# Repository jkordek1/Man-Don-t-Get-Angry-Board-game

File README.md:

# Man, Don't Get Angry - Board game

## About

Mensch ärgere Dich nicht (English: Man, Don't Get Angry) is a German board game developed by Josef Friedrich Schmidt in 1907/1908.
The name derives from the fact that a peg is sent back to the "out" field when another peg lands on it, similar to the later game Sorry!.

More information about the game can be found at the [wiki page](https://en.wikipedia.org/wiki/Mensch_%C3%A4rgere_Dich_nicht).

## Project idea
Idea of the project is to create an electronic version of the game to help promoting STEM education (and to have some fun of course).

## Project status
- [x] Breadboard prototype
- [x] Schematic
- [x] PCBs
- [x] Enclosure design
- [x] 3D CAD assembly and renders
- [x] Assembly
- [ ] Programming

## Issues
- no active issues

## Main features
- Based on popular ATmega328p microcontroller used on Arduino boards
- WS2812B-V5 addressable LEDs with no external components needed
- WS2812-mini addressable LED used as battery level indicator
- Touchpads connected via PCF8575 I/O Expander used as controls
- Piezo buzzer for audio queues
- 3000mAh rechargable Li-Po battery
- USB-C connector for charging and programming the microcontroller

## 3D renders

## Images

## PCBs
There are 3 different PCBs:

**BoardGame** - main 150x150mm PCB that contains LEDs and most of the electronic components (1 needed)

**Dice** - small PCB used as a touchpad (1 needed)

**Touchpad** - PCB with 3 touchpads used as controls for the game (4 needed)

## Enclosure
There are few 3D models files needed for enclosure:
1. Case - main part of the enclosure
2. FieldBoard - Upper part of the enclosure printed with black and white filaments

## Project folder structure
    .
    ├── ...
    ├── Images                  # Images of the project
    ├── Solidworks assembly     # Enclosure and PCB 3D model files
    ├── KiCad files             # Main folder
    │   ├── 3D models           # 3d models of components
    │   ├── BoardGame           # KiCAD project for main PCB
    │   ├── Dice                # KiCAD project for dice
    │   └── Touchpad            # KiCAD project for touchpad controls
    └── ...

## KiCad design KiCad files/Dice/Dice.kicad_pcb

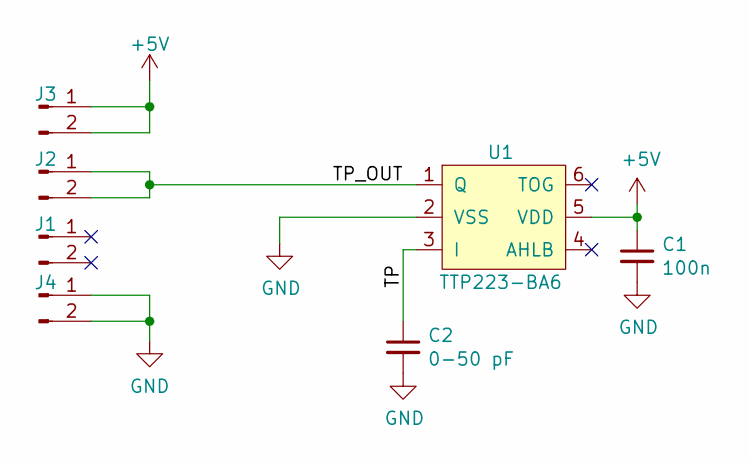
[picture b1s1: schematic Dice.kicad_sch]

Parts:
C1: 100n; C_0603_1608Metric
C2: 0-50 pF; C_0603_1608Metric
J1, J2, J3, J4: Conn_01x02_Male; PinHeader_1x02_P1.27mm_Vertical_SMD_Pin1Left
U1: TTP223-BA6; SOT-23-6

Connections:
+5V: C1.1, J3.1, J3.2, U1.5 (VDD)
/TP: C2.1, U1.3 (I)
/TP_OUT: J2.1, J2.2, U1.1 (Q)
GND: C1.2, C2.2, J4.1, J4.2, U1.2 (VSS)

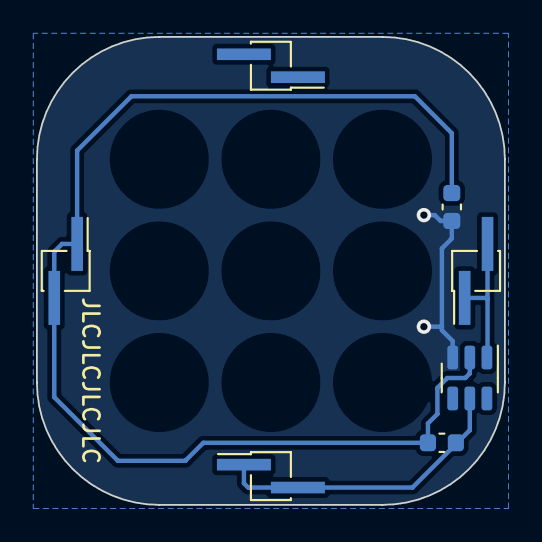
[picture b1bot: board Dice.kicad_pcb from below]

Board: 2 copper layers, 26.0 x 26.0 mm, 7 parts (7 on the bottom side), 4 nets.

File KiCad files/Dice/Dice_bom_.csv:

Component,Description,Part,References,Value,Footprint,Quantity Per PCB,Datasheet
1,"Unpolarized capacitor, small symbol",C_Small,C1,100n,C_0603_1608Metric,1,~
2,"Unpolarized capacitor, small symbol",C_Small,C2,0-50 pF,C_0603_1608Metric,1,~
3,"Generic connector, single row, 01x02, script generated (kicad-library-utils/schlib/autogen/connector/)",Conn_01x02_Male,J1 J2 J3 J4,Conn_01x02_Male,PinHeader_1x02_P1.27mm_Vertical_SMD_Pin1Left,4,~
4,,TTP223-BA6,U1,TTP223-BA6,SOT-23-6,1,





Component Groups:,4
Component Count:,7
Fitted Components:,7
Number of PCBs:,1
Total components:,7
Schematic Version:,
Schematic Date:,
PCB Variant:,default
BoM Date:,10.1.2023. 13:12:25
Schematic Source:,Dice.kicad_sch
KiCad Version:,Eeschema (6.0.10)

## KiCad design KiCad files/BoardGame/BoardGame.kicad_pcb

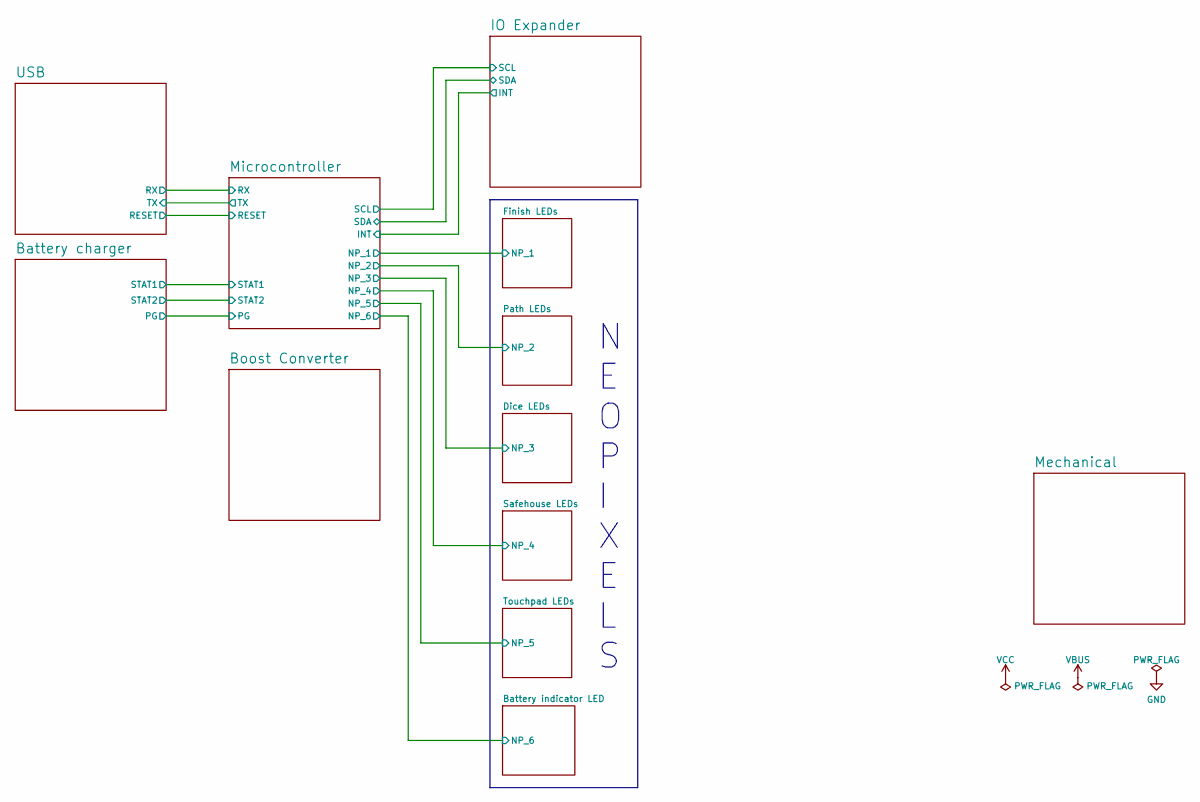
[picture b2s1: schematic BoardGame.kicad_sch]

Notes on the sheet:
N E O P I X E L S

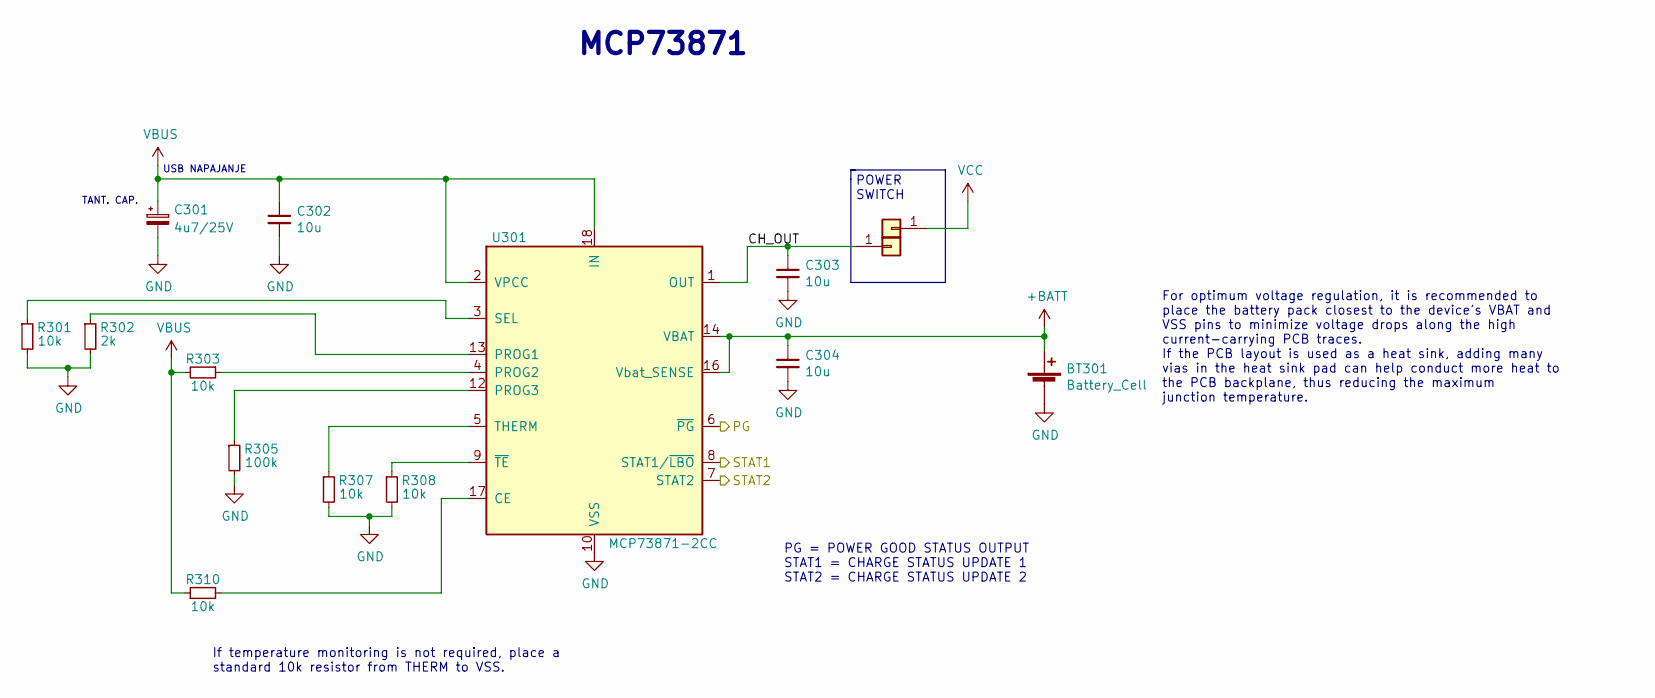
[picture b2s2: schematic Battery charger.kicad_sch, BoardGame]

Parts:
BT301: Battery_Cell; battery_103565_3000mah
C301: 4u7/25V; CP_EIA-3528-21_Kemet-B; JLCPCB Part # C2798040
C302, C303, C304: 10u; C_0805_2012Metric; JLCPCB Part # C237493
J301, J302: Conn_01x01; PinHeader_1x01
R301, R303, R307, R308, R310: 10k; R_0603_1608Metric
R302: 2k; R_0603_1608Metric; JLCPCB Part # C25590
R305: 100k; R_0603_1608Metric
U301: MCP73871-2CC; QFN-20-1EP_4x4mm_P0.5mm_EP2.5x2.5mm

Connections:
+BATT: BT301.1 (+), C304.1, U301.14 (VBAT), U301.15 (VBAT), U301.16 (Vbat_SENSE)
/Battery charger/CH_OUT: C303.1, J302.1, U301.1 (OUT), U301.20 (OUT)
/Battery charger/PG: U301.6 (~PG); also elsewhere on the board
/Battery charger/STAT1: U301.8 (STAT1/~LBO); also elsewhere on the board
/Battery charger/STAT2: U301.7 (STAT2); also elsewhere on the board
GND: BT301.2 (-), C301.2, C302.2, C303.2, C304.2, R301.2, R302.2, R305.2, R307.2, R308.2, U301.10 (VSS), U301.11 (VSS), U301.21 (VSS); also elsewhere on the board
unnamed: R310.2, U301.17 (CE)
unnamed: R302.1, U301.13 (PROG1)
unnamed: R303.1, U301.4 (PROG2)
unnamed: R305.1, U301.12 (PROG3)
unnamed: R301.1, U301.3 (SEL)
unnamed: R307.1, U301.5 (THERM)
unnamed: R308.1, U301.9 (~TE)
VBUS: C301.1, C302.1, R303.2, R310.1, U301.2 (VPCC), U301.18 (IN), U301.19 (IN); also elsewhere on the board
VCC: J301.1; also elsewhere on the board

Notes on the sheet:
PG = POWER GOOD STATUS OUTPUT STAT1 = CHARGE STATUS UPDATE 1 STAT2 = CHARGE STATUS UPDATE 2
TANT. CAP.
USB NAPAJANJE
POWER SWITCH
For optimum voltage regulation, it is recommended to place the battery pack closest to the device's VBAT and VSS pins to minimize voltage drops along the high current-carrying PCB traces. If the PCB layout is used as a heat sink, adding many vias in the heat sink pad can help conduct more heat to t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
MCP73871
If temperature monitoring is not required, place a standard 10k resistor from THERM to VSS.

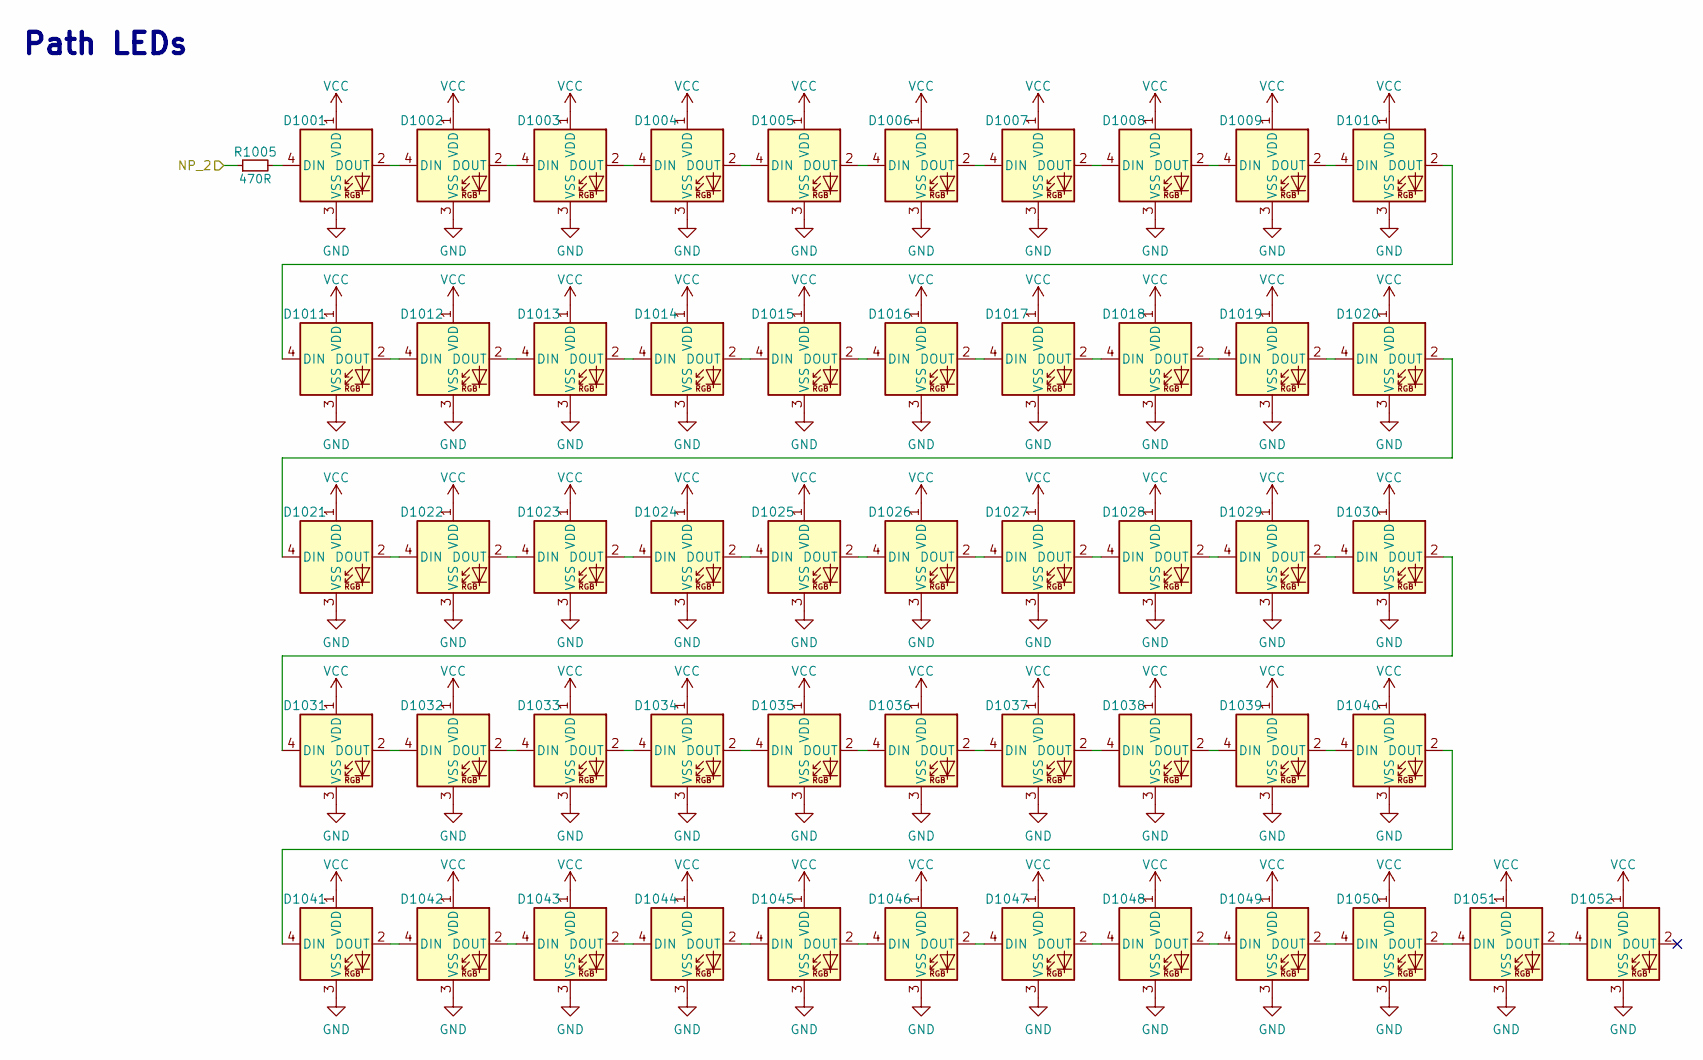
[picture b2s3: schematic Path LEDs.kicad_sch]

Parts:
D1001, D1002, D1003, D1004, D1005, D1006, D1007, D1008, D1009, D1010, D1011, D1012, D1013, D1014, D1015, D1016, D1017, D1018, D1019, D1020, D1021, D1022, D1023, D1024, D1025, D1026, D1027, D1028, D1029, D1030, D1031, D1032, D1033, D1034, D1035, D1036, D1037, D1038, D1039, D1040, D1041, D1042, D1043, D1044, D1045, D1046, D1047, D1048, D1049, D1050, D1051, D1052: WS2812B; LED_WS2812B_edited
R1005: 470R; R_0603_1608Metric

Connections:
/Microcontroller/NP_2: R1005.1; also elsewhere on the board
GND: D1001.3 (VSS), D1002.3 (VSS), D1003.3 (VSS), D1004.3 (VSS), D1005.3 (VSS), D1006.3 (VSS), D1007.3 (VSS), D1008.3 (VSS), D1009.3 (VSS), D1010.3 (VSS), D1011.3 (VSS), D1012.3 (VSS), D1013.3 (VSS), D1014.3 (VSS), D1015.3 (VSS), D1016.3 (VSS), D1017.3 (VSS), D1018.3 (VSS), D1019.3 (VSS), D1020.3 (VSS), D1021.3 (VSS), D1022.3 (VSS), D1023.3 (VSS), D1024.3 (VSS), D1025.3 (VSS), D1026.3 (VSS), D1027.3 (VSS), D1028.3 (VSS), D1029.3 (VSS), D1030.3 (VSS), D1031.3 (VSS), D1032.3 (VSS), D1033.3 (VSS), D1034.3 (VSS), D1035.3 (VSS), D1036.3 (VSS), D1037.3 (VSS), D1038.3 (VSS), D1039.3 (VSS), D1040.3 (VSS), D1041.3 (VSS), D1042.3 (VSS), D1043.3 (VSS), D1044.3 (VSS), D1045.3 (VSS), D1046.3 (VSS), D1047.3 (VSS), D1048.3 (VSS), D1049.3 (VSS), D1050.3 (VSS), D1051.3 (VSS), D1052.3 (VSS); also elsewhere on the board
unnamed: D1001.4 (DIN), R1005.2
unnamed: D1001.2 (DOUT), D1002.4 (DIN)
unnamed: D1002.2 (DOUT), D1003.4 (DIN)
unnamed: D1003.2 (DOUT), D1004.4 (DIN)
unnamed: D1004.2 (DOUT), D1005.4 (DIN)
unnamed: D1005.2 (DOUT), D1006.4 (DIN)
unnamed: D1006.2 (DOUT), D1007.4 (DIN)
unnamed: D1007.2 (DOUT), D1008.4 (DIN)
unnamed: D1008.2 (DOUT), D1009.4 (DIN)
unnamed: D1009.2 (DOUT), D1010.4 (DIN)
unnamed: D1010.2 (DOUT), D1011.4 (DIN)
unnamed: D1011.2 (DOUT), D1012.4 (DIN)
unnamed: D1012.2 (DOUT), D1013.4 (DIN)
unnamed: D1013.2 (DOUT), D1014.4 (DIN)
unnamed: D1014.2 (DOUT), D1015.4 (DIN)
unnamed: D1015.2 (DOUT), D1016.4 (DIN)
unnamed: D1016.2 (DOUT), D1017.4 (DIN)
unnamed: D1017.2 (DOUT), D1018.4 (DIN)
unnamed: D1018.2 (DOUT), D1019.4 (DIN)
unnamed: D1019.2 (DOUT), D1020.4 (DIN)
unnamed: D1020.2 (DOUT), D1021.4 (DIN)
unnamed: D1021.2 (DOUT), D1022.4 (DIN)
unnamed: D1022.2 (DOUT), D1023.4 (DIN)
unnamed: D1023.2 (DOUT), D1024.4 (DIN)
unnamed: D1024.2 (DOUT), D1025.4 (DIN)
unnamed: D1025.2 (DOUT), D1026.4 (DIN)
unnamed: D1026.2 (DOUT), D1027.4 (DIN)
unnamed: D1027.2 (DOUT), D1028.4 (DIN)
unnamed: D1028.2 (DOUT), D1029.4 (DIN)
unnamed: D1029.2 (DOUT), D1030.4 (DIN)
unnamed: D1030.2 (DOUT), D1031.4 (DIN)
unnamed: D1031.2 (DOUT), D1032.4 (DIN)
unnamed: D1032.2 (DOUT), D1033.4 (DIN)
unnamed: D1033.2 (DOUT), D1034.4 (DIN)
unnamed: D1034.2 (DOUT), D1035.4 (DIN)
unnamed: D1035.2 (DOUT), D1036.4 (DIN)
unnamed: D1036.2 (DOUT), D1037.4 (DIN)
unnamed: D1037.2 (DOUT), D1038.4 (DIN)
unnamed: D1038.2 (DOUT), D1039.4 (DIN)
unnamed: D1039.2 (DOUT), D1040.4 (DIN)
unnamed: D1040.2 (DOUT), D1041.4 (DIN)
unnamed: D1041.2 (DOUT), D1042.4 (DIN)
unnamed: D1042.2 (DOUT), D1043.4 (DIN)
unnamed: D1043.2 (DOUT), D1044.4 (DIN)
unnamed: D1044.2 (DOUT), D1045.4 (DIN)
unnamed: D1045.2 (DOUT), D1046.4 (DIN)
unnamed: D1046.2 (DOUT), D1047.4 (DIN)
unnamed: D1047.2 (DOUT), D1048.4 (DIN)
unnamed: D1048.2 (DOUT), D1049.4 (DIN)
unnamed: D1049.2 (DOUT), D1050.4 (DIN)
unnamed: D1050.2 (DOUT), D1051.4 (DIN)
unnamed: D1051.2 (DOUT), D1052.4 (DIN)
VCC: D1001.1 (VDD), D1002.1 (VDD), D1003.1 (VDD), D1004.1 (VDD), D1005.1 (VDD), D1006.1 (VDD), D1007.1 (VDD), D1008.1 (VDD), D1009.1 (VDD), D1010.1 (VDD), D1011.1 (VDD), D1012.1 (VDD), D1013.1 (VDD), D1014.1 (VDD), D1015.1 (VDD), D1016.1 (VDD), D1017.1 (VDD), D1018.1 (VDD), D1019.1 (VDD), D1020.1 (VDD), D1021.1 (VDD), D1022.1 (VDD), D1023.1 (VDD), D1024.1 (VDD), D1025.1 (VDD), D1026.1 (VDD), D1027.1 (VDD), D1028.1 (VDD), D1029.1 (VDD), D1030.1 (VDD), D1031.1 (VDD), D1032.1 (VDD), D1033.1 (VDD), D1034.1 (VDD), D1035.1 (VDD), D1036.1 (VDD), D1037.1 (VDD), D1038.1 (VDD), D1039.1 (VDD), D1040.1 (VDD), D1041.1 (VDD), D1042.1 (VDD), D1043.1 (VDD), D1044.1 (VDD), D1045.1 (VDD), D1046.1 (VDD), D1047.1 (VDD), D1048.1 (VDD), D1049.1 (VDD), D1050.1 (VDD), D1051.1 (VDD), D1052.1 (VDD); also elsewhere on the board

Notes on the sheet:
Path LEDs

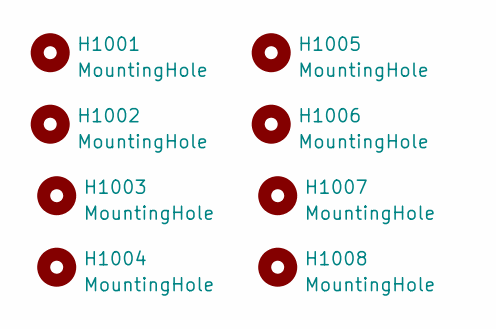
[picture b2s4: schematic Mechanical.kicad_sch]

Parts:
H1001, H1002, H1003, H1004, H1005, H1006, H1007, H1008: MountingHole; MountingHole_3.2mm_M3

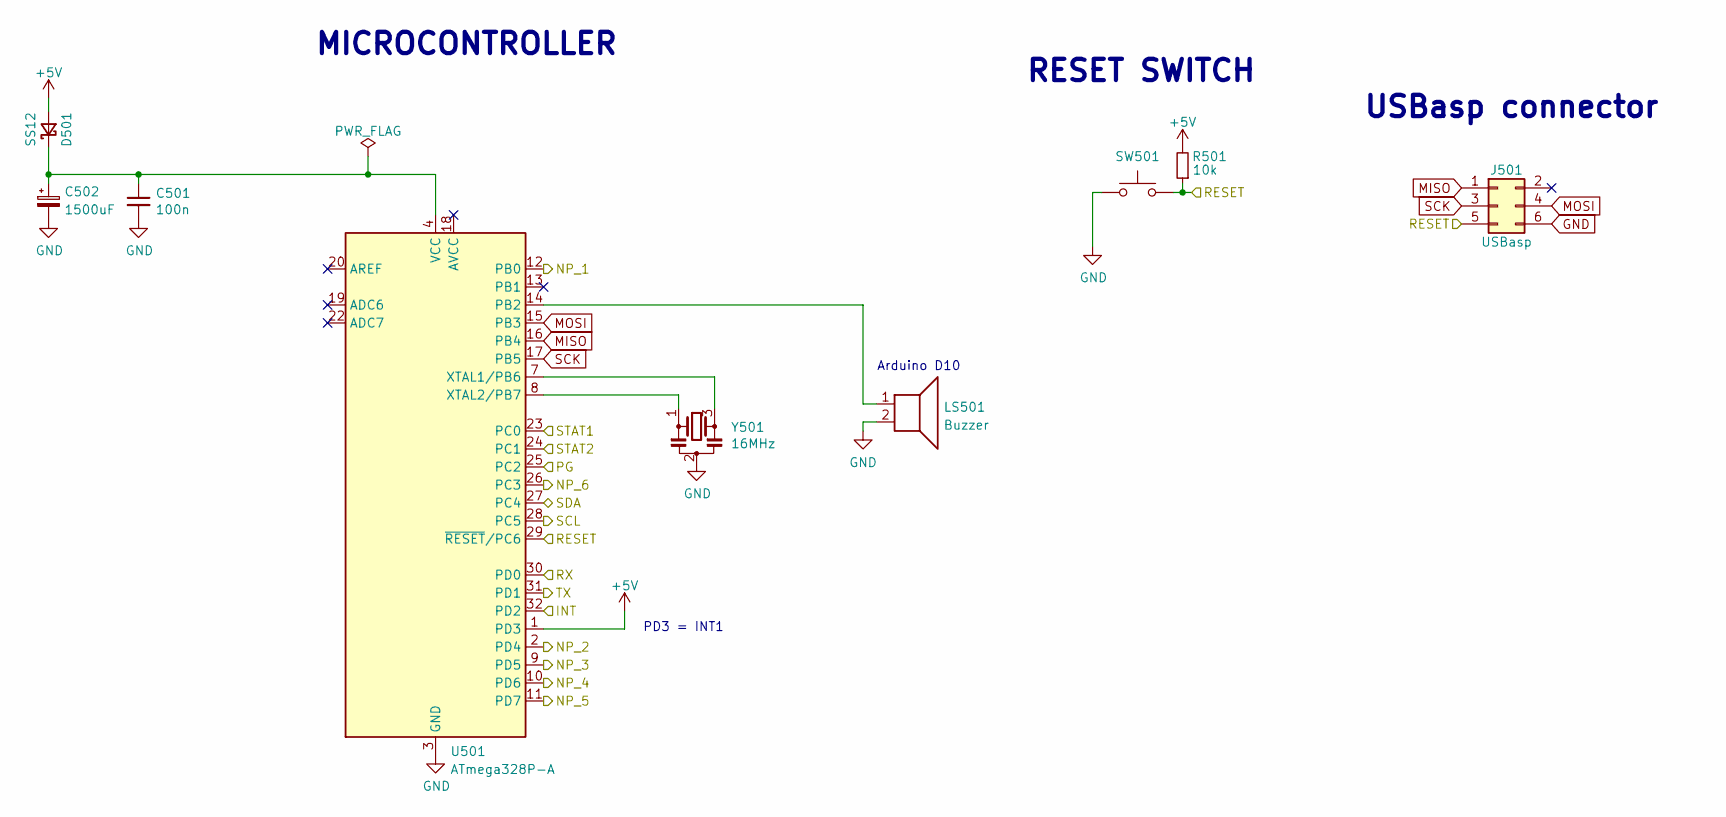
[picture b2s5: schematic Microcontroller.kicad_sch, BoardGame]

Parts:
C501: 100n; C_0603_1608Metric; JLCPCB Part # C113803
C502: 1500uF; CP_EIA-7343-31_Kemet-D
D501: SS12; D_SMA; JLCPCB Part # C2985002
J501: USBasp; PinHeader_2x03_P1.27mm_Vertical_SMD
LS501: Buzzer; KLJ-1102
R501: 10k; R_0603_1608Metric
SW501: SW_Push; SW_SPST_TL3342; JLCPCB Part # C2886894
U501: ATmega328P-A; TQFP-32_7x7mm_P0.8mm
Y501: 16MHz; CSTCE16M0V53-R0; JLCPCB Part # C32180

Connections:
+5V: D501.2 (A), R501.2, U501.1 (PD3); also elsewhere on the board
/Battery charger/PG: U501.25 (PC2); also elsewhere on the board
/Battery charger/STAT1: U501.23 (PC0); also elsewhere on the board
/Battery charger/STAT2: U501.24 (PC1); also elsewhere on the board
/Battery indicator LED/NP_6: U501.26 (PC3); also elsewhere on the board
/Dice LEDs/NP_3: U501.9 (PD5); also elsewhere on the board
/Finish LEDs/NP_1: U501.12 (PB0); also elsewhere on the board
/IO Expander/INT: U501.32 (PD2); also elsewhere on the board
/IO Expander/SCL: U501.28 (PC5); also elsewhere on the board
/IO Expander/SDA: U501.27 (PC4); also elsewhere on the board
/Microcontroller/NP_2: U501.2 (PD4); also elsewhere on the board
/Microcontroller/NP_4: U501.10 (PD6); also elsewhere on the board
/Microcontroller/NP_5: U501.11 (PD7); also elsewhere on the board
/Microcontroller/RESET: J501.5, R501.1, SW501.2, U501.29 (~RESET/PC6); also elsewhere on the board
/Microcontroller/RX: U501.30 (PD0); also elsewhere on the board
/Microcontroller/TX: U501.31 (PD1); also elsewhere on the board
GND: C501.2, C502.2, J501.6, LS501.2, SW501.1, U501.3 (GND), U501.5 (GND), U501.21 (GND), Y501.2; also elsewhere on the board
MISO: J501.1, U501.16 (PB4)
MOSI: J501.4, U501.15 (PB3)
unnamed: C501.1, C502.1, D501.1 (K), U501.4 (VCC), U501.6 (VCC)
unnamed: LS501.1, U501.14 (PB2)
unnamed: U501.7 (XTAL1/PB6), Y501.3
unnamed: U501.8 (XTAL2/PB7), Y501.1
SCK: J501.3, U501.17 (PB5)

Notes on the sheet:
MICROCONTROLLER
USBasp connector
PD3 = INT1
Arduino D10
RESET SWITCH

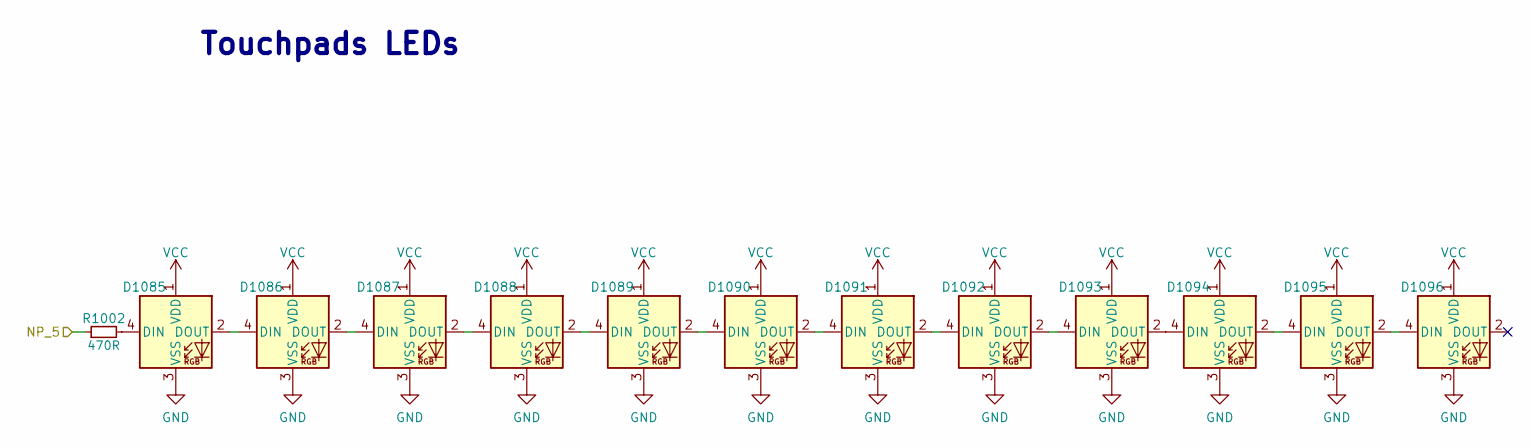
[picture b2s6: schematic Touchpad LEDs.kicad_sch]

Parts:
D1085, D1086, D1087, D1088, D1089, D1090, D1091, D1092, D1093, D1094, D1095, D1096: WS2812B; LED_WS2812B_edited
R1002: 470R; R_0603_1608Metric

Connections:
/Microcontroller/NP_5: R1002.1; also elsewhere on the board
GND: D1085.3 (VSS), D1086.3 (VSS), D1087.3 (VSS), D1088.3 (VSS), D1089.3 (VSS), D1090.3 (VSS), D1091.3 (VSS), D1092.3 (VSS), D1093.3 (VSS), D1094.3 (VSS), D1095.3 (VSS), D1096.3 (VSS); also elsewhere on the board
unnamed: D1085.4 (DIN), R1002.2
unnamed: D1085.2 (DOUT), D1086.4 (DIN)
unnamed: D1086.2 (DOUT), D1087.4 (DIN)
unnamed: D1087.2 (DOUT), D1088.4 (DIN)
unnamed: D1088.2 (DOUT), D1089.4 (DIN)
unnamed: D1089.2 (DOUT), D1090.4 (DIN)
unnamed: D1090.2 (DOUT), D1091.4 (DIN)
unnamed: D1091.2 (DOUT), D1092.4 (DIN)
unnamed: D1092.2 (DOUT), D1093.4 (DIN)
unnamed: D1093.2 (DOUT), D1094.4 (DIN)
unnamed: D1094.2 (DOUT), D1095.4 (DIN)
unnamed: D1095.2 (DOUT), D1096.4 (DIN)
VCC: D1085.1 (VDD), D1086.1 (VDD), D1087.1 (VDD), D1088.1 (VDD), D1089.1 (VDD), D1090.1 (VDD), D1091.1 (VDD), D1092.1 (VDD), D1093.1 (VDD), D1094.1 (VDD), D1095.1 (VDD), D1096.1 (VDD); also elsewhere on the board

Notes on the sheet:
Touchpads LEDs

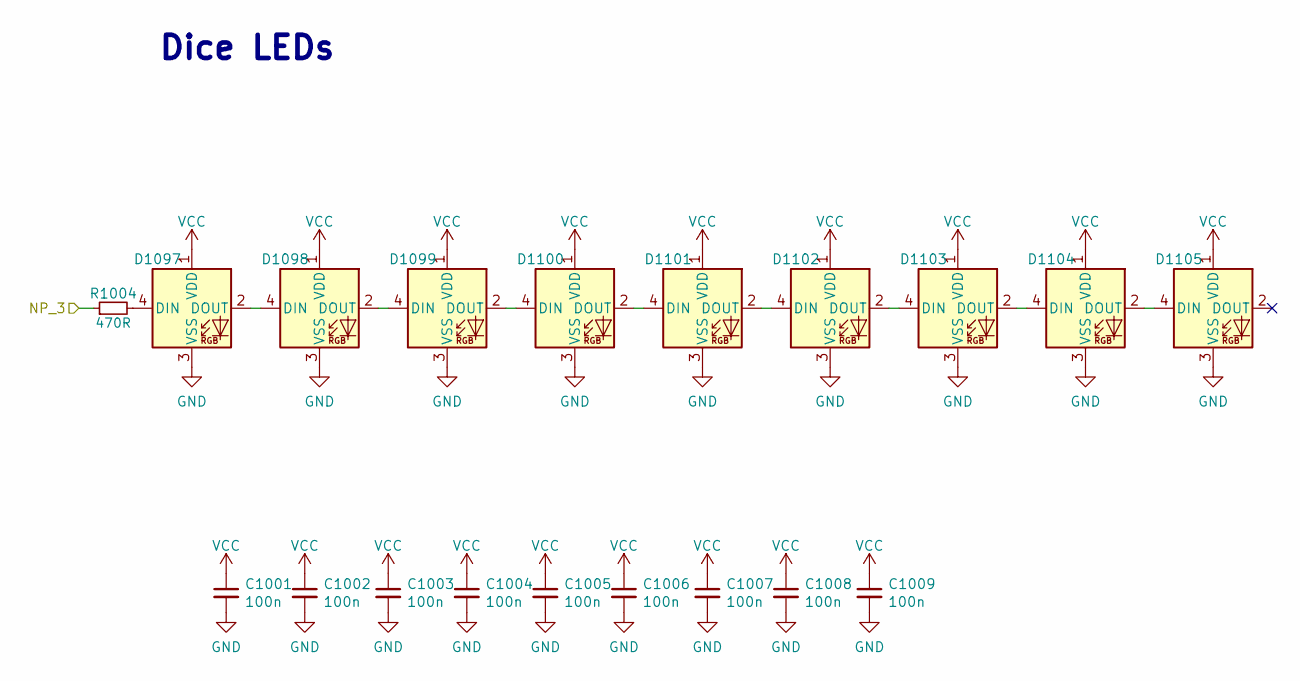
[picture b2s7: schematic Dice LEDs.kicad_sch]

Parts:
C1001, C1002, C1003, C1004, C1005, C1006, C1007, C1008, C1009: 100n; C_0603_1608Metric; JLCPCB Part # C113803
D1097, D1098, D1099, D1100, D1101, D1102, D1103, D1104, D1105: WS2812B; WS2812-mini; JLCPCB Part # C527089
R1004: 470R; R_0603_1608Metric

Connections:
/Dice LEDs/NP_3: R1004.1; also elsewhere on the board
GND: C1001.2, C1002.2, C1003.2, C1004.2, C1005.2, C1006.2, C1007.2, C1008.2, C1009.2, D1097.3 (VSS), D1098.3 (VSS), D1099.3 (VSS), D1100.3 (VSS), D1101.3 (VSS), D1102.3 (VSS), D1103.3 (VSS), D1104.3 (VSS), D1105.3 (VSS); also elsewhere on the board
unnamed: D1097.4 (DIN), R1004.2
unnamed: D1097.2 (DOUT), D1098.4 (DIN)
unnamed: D1098.2 (DOUT), D1099.4 (DIN)
unnamed: D1099.2 (DOUT), D1100.4 (DIN)
unnamed: D1100.2 (DOUT), D1101.4 (DIN)
unnamed: D1101.2 (DOUT), D1102.4 (DIN)
unnamed: D1102.2 (DOUT), D1103.4 (DIN)
unnamed: D1103.2 (DOUT), D1104.4 (DIN)
unnamed: D1104.2 (DOUT), D1105.4 (DIN)
VCC: C1001.1, C1002.1, C1003.1, C1004.1, C1005.1, C1006.1, C1007.1, C1008.1, C1009.1, D1097.1 (VDD), D1098.1 (VDD), D1099.1 (VDD), D1100.1 (VDD), D1101.1 (VDD), D1102.1 (VDD), D1103.1 (VDD), D1104.1 (VDD), D1105.1 (VDD); also elsewhere on the board

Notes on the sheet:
Dice LEDs

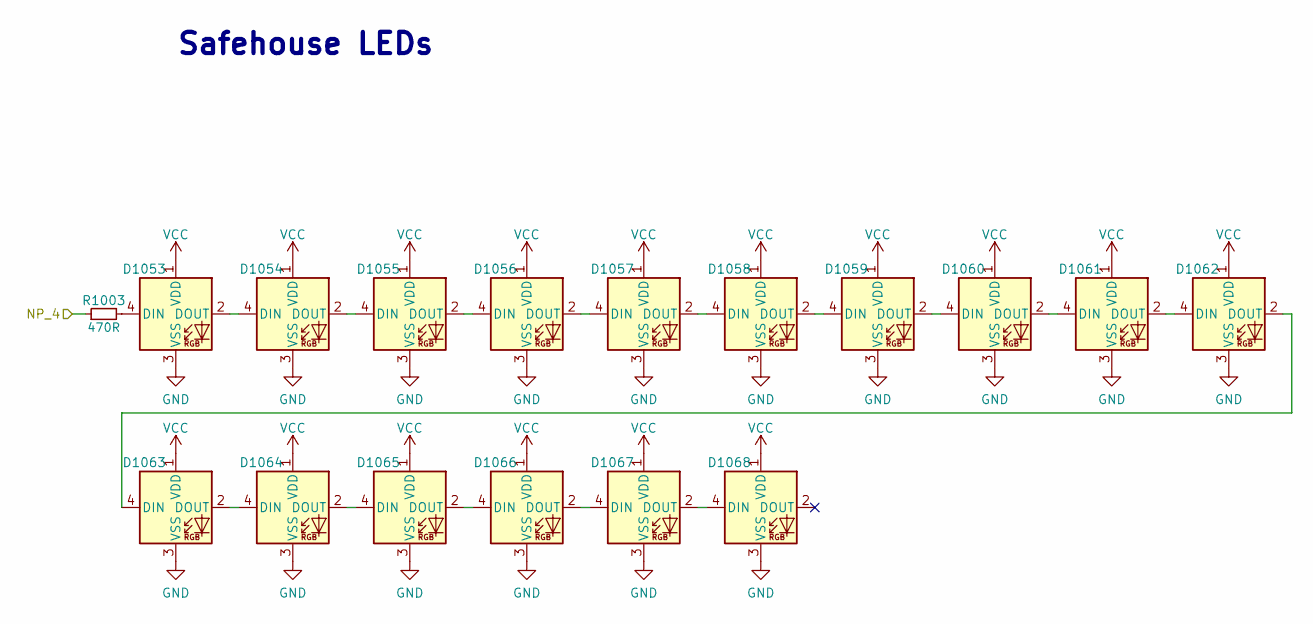
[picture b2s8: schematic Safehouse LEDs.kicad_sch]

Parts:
D1053, D1054, D1055, D1056, D1057, D1058, D1059, D1060, D1061, D1062, D1063, D1064, D1065, D1066, D1067, D1068: WS2812B; LED_WS2812B_edited
R1003: 470R; R_0603_1608Metric

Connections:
/Microcontroller/NP_4: R1003.1; also elsewhere on the board
GND: D1053.3 (VSS), D1054.3 (VSS), D1055.3 (VSS), D1056.3 (VSS), D1057.3 (VSS), D1058.3 (VSS), D1059.3 (VSS), D1060.3 (VSS), D1061.3 (VSS), D1062.3 (VSS), D1063.3 (VSS), D1064.3 (VSS), D1065.3 (VSS), D1066.3 (VSS), D1067.3 (VSS), D1068.3 (VSS); also elsewhere on the board
unnamed: D1053.4 (DIN), R1003.2
unnamed: D1053.2 (DOUT), D1054.4 (DIN)
unnamed: D1054.2 (DOUT), D1055.4 (DIN)
unnamed: D1055.2 (DOUT), D1056.4 (DIN)
unnamed: D1056.2 (DOUT), D1057.4 (DIN)
unnamed: D1057.2 (DOUT), D1058.4 (DIN)
unnamed: D1058.2 (DOUT), D1059.4 (DIN)
unnamed: D1059.2 (DOUT), D1060.4 (DIN)
unnamed: D1060.2 (DOUT), D1061.4 (DIN)
unnamed: D1061.2 (DOUT), D1062.4 (DIN)
unnamed: D1062.2 (DOUT), D1063.4 (DIN)
unnamed: D1063.2 (DOUT), D1064.4 (DIN)
unnamed: D1064.2 (DOUT), D1065.4 (DIN)
unnamed: D1065.2 (DOUT), D1066.4 (DIN)
unnamed: D1066.2 (DOUT), D1067.4 (DIN)
unnamed: D1067.2 (DOUT), D1068.4 (DIN)
VCC: D1053.1 (VDD), D1054.1 (VDD), D1055.1 (VDD), D1056.1 (VDD), D1057.1 (VDD), D1058.1 (VDD), D1059.1 (VDD), D1060.1 (VDD), D1061.1 (VDD), D1062.1 (VDD), D1063.1 (VDD), D1064.1 (VDD), D1065.1 (VDD), D1066.1 (VDD), D1067.1 (VDD), D1068.1 (VDD); also elsewhere on the board

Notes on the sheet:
Safehouse LEDs

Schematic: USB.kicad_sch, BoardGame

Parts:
C201, C202, C204: 100n; C_0603_1608Metric; JLCPCB Part # C113803
C203: 10u; CP_EIA-3528-21_Kemet-B; JLCPCB Part # C2798040
FB201: 100 @ 100MHz; R_0603_1608Metric; JLCPCB Part # C107332
J201: USB_C_Receptacle_USB2.0; USB_C_Receptacle_HRO_TYPE-C-31-M-12
R201, R204: 1k; R_0603_1608Metric
R202, R203: 5k1; R_0603_1608Metric; JLCPCB Part # C3017721
U201: USBLC6-2SC6; SOT-23-6; JLCPCB Part # C3029034
U202: CH340C; SOIC-16_3.9x9.9mm_P1.27mm

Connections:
/Microcontroller/RESET: C204.1; also elsewhere on the board
/Microcontroller/RX: R201.1; also elsewhere on the board
/Microcontroller/TX: R204.1; also elsewhere on the board
/USB/USB: FB201.1, J201.A4 (VBUS), J201.A9 (VBUS), J201.B4 (VBUS), J201.B9 (VBUS)
GND: C201.2, C202.2, C203.2, J201.A1 (GND), J201.A12 (GND), J201.B1 (GND), J201.B12 (GND), R202.2, R203.2, U201.2 (GND), U202.1 (GND); also elsewhere on the board
unnamed: J201.A5 (CC1), R203.1
unnamed: J201.B5 (CC2), R202.1
unnamed: R204.2, U202.3 (RXD)
unnamed: R201.2, U202.2 (TXD)
unnamed: C201.1, U202.4 (V3)
unnamed: C204.2, U202.13 (~DTR)
USB_CONN_D+: J201.A6 (D+), J201.B6 (D+), U201.3 (I/O2)
USB_CONN_D-: J201.A7 (D-), J201.B7 (D-), U201.1 (I/O1)
USB_D+: U201.4 (I/O2), U202.5 (UD+)
USB_D-: U201.6 (I/O1), U202.6 (UD-)
VBUS: C202.1, C203.1, FB201.2, U201.5 (VBUS), U202.16 (VCC); also elsewhere on the board

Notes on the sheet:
Shield is grounded at the host side (PC) so NC here.
CH340C USB-UART IC
ESD protection IC
The device must have 5.1k pull-down on the its port CC pin (on both pins). Once the C-C cable is connected between two link partners, the DFP (host) will sense the drag by 5.1k resistor (from device side). As result, it will turn the VBUS on. This is how a host recognizes that a connection has been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
SBU1/SBU2: these are low-speed lines used only for Alternate Mode and accessory mode. For example, with DisplayPort, AUX+/AUX– transmit over the SBU lines. For audio adapter accessory mode, these lines are used for the microphone input and analog GND.
Ferrite bead needs to be placed close to USB connector on PCB

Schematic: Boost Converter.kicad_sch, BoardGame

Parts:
C601, C602: 22u / 16V; C_1210_3225Metric; JLCPCB Part # C337451
D601: SS12; D_SMA; JLCPCB Part # C2985002
L601: 4R7; Inductor_4mm(5x5mm pads)
R601: 100k; R_0603_1608Metric
R602: 13k3; R_0603_1608Metric; JLCPCB Part # C185373
U601: MT3608; SOT-23-6; JLCPCB Part # C2932326

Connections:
+5V: C602.1, D601.1 (K), R601.1; also elsewhere on the board
/Boost Converter/FB: R601.2, R602.1, U601.3 (FB)
/Boost Converter/L_OUT: D601.2 (A), L601.2, U601.1 (SW)
GND: C601.2, C602.2, R602.2, U601.2 (GND); also elsewhere on the board
VCC: C601.1, L601.1, U601.4 (EN), U601.5 (IN); also elsewhere on the board

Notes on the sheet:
Input and output ceramic capacitors of 22μF are recommended. For better voltage filtering, ceramic capacitors with low ESR are recommended (X7R).
Schottky diode is a good choice for MT3608 because of its low forward voltage drop and fast reverses recovery.
The recommended values of inductor are 4.7 to 22μH. The inductor should have low core loss at 1.2MHz and low DCR for better efficiency.
The internal reference V_{REF} is 0.6V (Typical). V_{OUT} = V_{REF} * (1 + R_{1}/R_{2}) V_{OUT} = 0.6 * (1 + 100k/13.3k) = 5.11V

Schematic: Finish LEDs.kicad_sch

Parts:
D1069, D1070, D1071, D1072, D1073, D1074, D1075, D1076, D1077, D1078, D1079, D1080, D1081, D1082, D1083, D1084: WS2812B; LED_WS2812B_edited
R1001: 470R; R_0603_1608Metric

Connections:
/Finish LEDs/NP_1: R1001.1; also elsewhere on the board
GND: D1069.3 (VSS), D1070.3 (VSS), D1071.3 (VSS), D1072.3 (VSS), D1073.3 (VSS), D1074.3 (VSS), D1075.3 (VSS), D1076.3 (VSS), D1077.3 (VSS), D1078.3 (VSS), D1079.3 (VSS), D1080.3 (VSS), D1081.3 (VSS), D1082.3 (VSS), D1083.3 (VSS), D1084.3 (VSS); also elsewhere on the board
unnamed: D1069.4 (DIN), R1001.2
unnamed: D1069.2 (DOUT), D1070.4 (DIN)
unnamed: D1070.2 (DOUT), D1071.4 (DIN)
unnamed: D1071.2 (DOUT), D1072.4 (DIN)
unnamed: D1072.2 (DOUT), D1073.4 (DIN)
unnamed: D1073.2 (DOUT), D1074.4 (DIN)
unnamed: D1074.2 (DOUT), D1075.4 (DIN)
unnamed: D1075.2 (DOUT), D1076.4 (DIN)
unnamed: D1076.2 (DOUT), D1077.4 (DIN)
unnamed: D1077.2 (DOUT), D1078.4 (DIN)
unnamed: D1078.2 (DOUT), D1079.4 (DIN)
unnamed: D1079.2 (DOUT), D1080.4 (DIN)
unnamed: D1080.2 (DOUT), D1081.4 (DIN)
unnamed: D1081.2 (DOUT), D1082.4 (DIN)
unnamed: D1082.2 (DOUT), D1083.4 (DIN)
unnamed: D1083.2 (DOUT), D1084.4 (DIN)
VCC: D1069.1 (VDD), D1070.1 (VDD), D1071.1 (VDD), D1072.1 (VDD), D1073.1 (VDD), D1074.1 (VDD), D1075.1 (VDD), D1076.1 (VDD), D1077.1 (VDD), D1078.1 (VDD), D1079.1 (VDD), D1080.1 (VDD), D1081.1 (VDD), D1082.1 (VDD), D1083.1 (VDD), D1084.1 (VDD); also elsewhere on the board

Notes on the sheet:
Finish LEDs

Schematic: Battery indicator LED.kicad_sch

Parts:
D1106: WS2812B; WS2812-mini
R1006: 470R; R_0603_1608Metric

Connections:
/Battery indicator LED/NP_6: R1006.1; also elsewhere on the board
GND: D1106.3 (VSS); also elsewhere on the board
unnamed: D1106.4 (DIN), R1006.2
VCC: D1106.1 (VDD); also elsewhere on the board

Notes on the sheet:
Battery LED

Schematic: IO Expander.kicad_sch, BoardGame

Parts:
C401: 100n; C_0603_1608Metric; JLCPCB Part # C113803
J401, J402, J403, J404: Conn_02x03_Odd_Even; 2x03_P1.27mm_conn
J405, J406, J407, J408: Conn_01x02_Female; PinHeader_1x02_P1.27mm_Vertical
R401, R402: 4k7; R_0603_1608Metric; JLCPCB Part # C114662
U401: PCF8575; SOIC-24W_7.5x15.4mm_P1.27mm

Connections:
+5V: C401.1, J401.3, J401.4, J402.3, J402.4, J403.3, J403.4, J404.3, J404.4, J405.1, J405.2, R401.1, R402.1, U401.24 (VCC); also elsewhere on the board
/IO Expander/INT: U401.1 (~INT); also elsewhere on the board
/IO Expander/SCL: R401.2, U401.22 (SCL); also elsewhere on the board
/IO Expander/SDA: R402.2, U401.23 (SDA); also elsewhere on the board
GND: C401.2, J401.1, J402.1, J403.1, J404.1, J406.1, J406.2, U401.12 (GND); also elsewhere on the board
TP_1: J401.2, U401.4 (P00)
TP_2: J401.6, U401.5 (P01)
TP_3: J401.5, U401.6 (P02)
TP_4: J402.2, U401.7 (P03)
TP_5: J402.6, U401.8 (P04)
TP_6: J402.5, U401.9 (P05)
TP_7: J403.2, U401.10 (P06)
TP_8: J403.6, U401.11 (P07)
TP_9: J403.5, U401.13 (P10)
TP_10: J404.2, U401.14 (P11)
TP_11: J404.6, U401.15 (P12)
TP_12: J404.5, U401.16 (P13)
TP_13: J408.1, J408.2, U401.17 (P14)

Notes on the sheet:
Dice touchpad connectors
Touchpad connectors
PCF8575 I/O Expander
